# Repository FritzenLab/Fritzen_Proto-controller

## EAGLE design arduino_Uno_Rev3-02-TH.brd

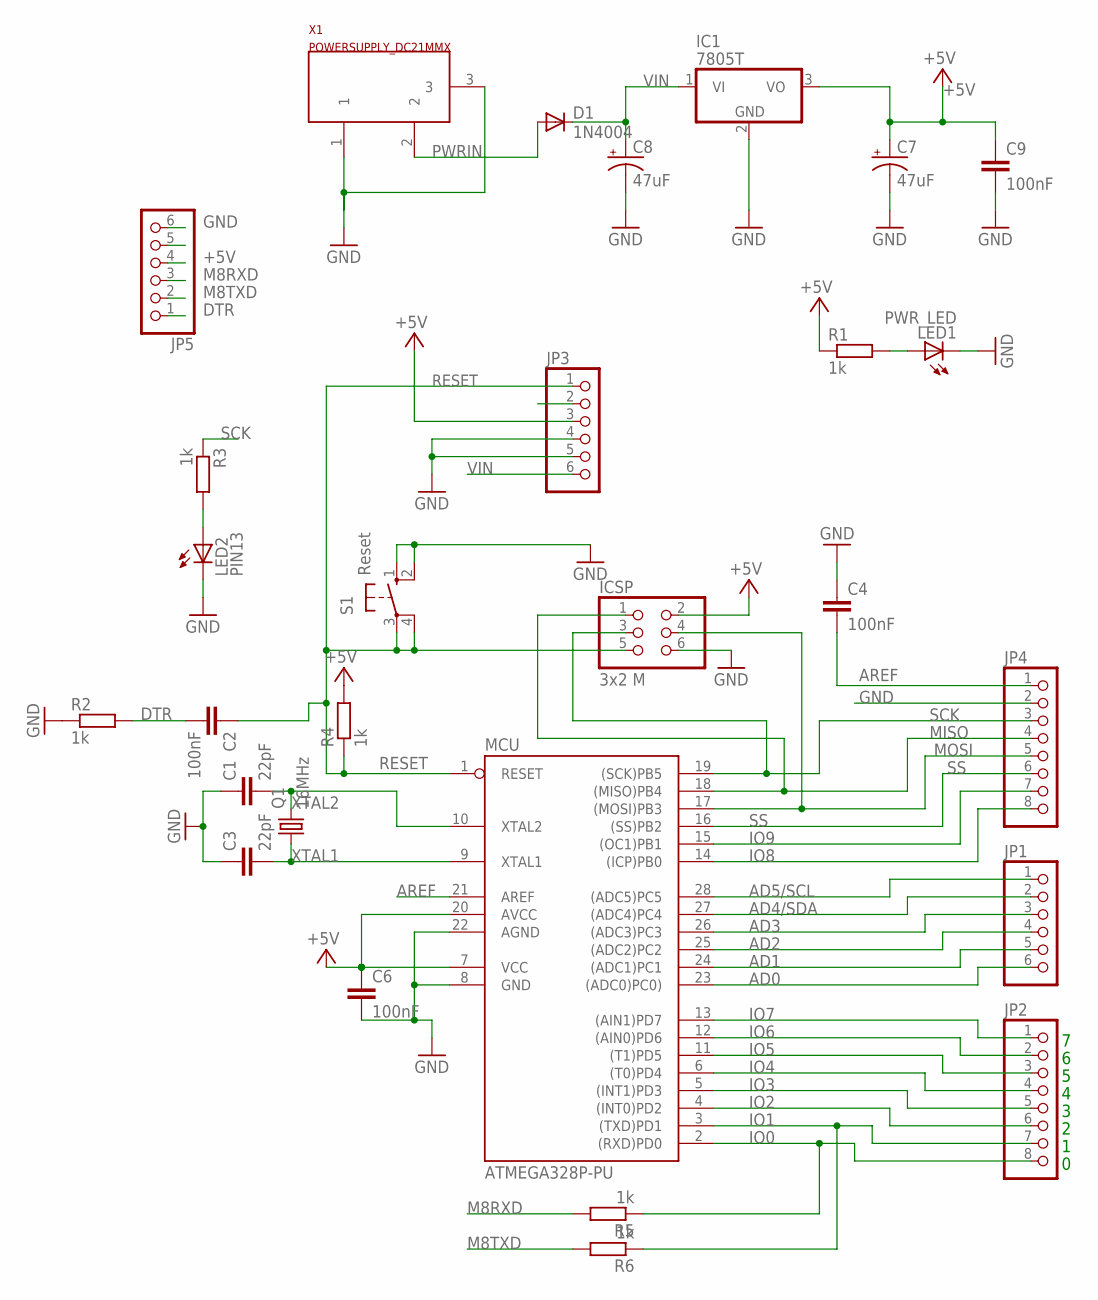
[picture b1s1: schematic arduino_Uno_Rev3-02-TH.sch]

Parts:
C1, C3: 22pF; C2.5-2
C2, C4, C6, C9: 100nF; C2.5-3
C7, C8: 47uF; E3,5-8
D1: 1N4004; DO41-10
IC1: 7805T; TO220H
ICSP: 3x2 M; 2X03
JP1, JP3, JP5: PINHD-1X6; 1X06
JP2, JP4: PINHD-1X8BIG; 1X08-BIG
LED1: PWR_LED; LED3MM
LED2: PIN13; LED5MM
MCU: ATMEGA328P-PU; DIL28-3
Q1: 16MHz; HC49/S
R1, R2, R3, R4, R5, R6: 1k; 0207/10
S1: Reset; B3F-10XX
X1: POWERSUPPLY_DC21MMX; POWERSUPPLY_DC-21MM

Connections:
+5V: C6.1, C7.+, C9.1, IC1.3 (VO), ICSP.2, JP3.3, JP5.4, MCU.7 (VCC), MCU.20 (AVCC), R1.1, R4.2
AD0: JP1.6, MCU.23 ((ADC0)PC0))
AD1: JP1.5, MCU.24 ((ADC1)PC1)
AD2: JP1.4, MCU.25 ((ADC2)PC2)
AD3: JP1.3, MCU.26 ((ADC3)PC3)
AD4/SDA: JP1.2, MCU.27 ((ADC4)PC4)
AD5/SCL: JP1.1, MCU.28 ((ADC5)PC5)
AREF: C4.2, JP4.1, MCU.21 (AREF)
DTR: C2.2, JP5.1, R2.2
GND: C1.1, C3.1, C4.1, C6.2, C7.-, C8.-, C9.2, IC1.2 (GND), ICSP.6, JP3.4, JP3.5, JP4.2, JP5.6, LED1.K (C), LED2.K (C), MCU.8 (GND), MCU.22 (AGND), R2.1, S1.1 (S), S1.2 (S1), X1.1, X1.3
IO0: JP2.8, MCU.2 ((RXD)PD0), R5.1
IO1: JP2.7, MCU.3 ((TXD)PD1), R6.1
IO2: JP2.6, MCU.4 ((INT0)PD2)
IO3: JP2.5, MCU.5 ((INT1)PD3)
IO4: JP2.4, MCU.6 ((T0)PD4)
IO5: JP2.3, MCU.11 ((T1)PD5)
IO6: JP2.2, MCU.12 ((AIN0)PD6)
IO7: JP2.1, MCU.13 ((AIN1)PD7)
IO8: JP4.8, MCU.14 ((ICP)PB0)
IO9: JP4.7, MCU.15 ((OC1)PB1)
M8RXD: JP5.3, R5.2
M8TXD: JP5.2, R6.2
MISO: ICSP.1, JP4.4, MCU.18 ((MISO)PB4)
MOSI: ICSP.4, JP4.5, MCU.17 ((MOSI)PB3)
unnamed: LED2.A, R3.2
unnamed: LED1.A, R1.2
PWRIN: D1.A, X1.2
RESET: C2.1, ICSP.5, JP3.1, MCU.1 (RESET), R4.1, S1.3, S1.4 (P1)
SCK: ICSP.3, JP4.3, MCU.19 ((SCK)PB5), R3.1
SS: JP4.6, MCU.16 ((SS)PB2)
VIN: C8.+, D1.C, IC1.1 (VI), JP3.6
XTAL1: C3.2, MCU.9 (XTAL1), Q1.1
XTAL2: C1.2, MCU.10 (XTAL2), Q1.2

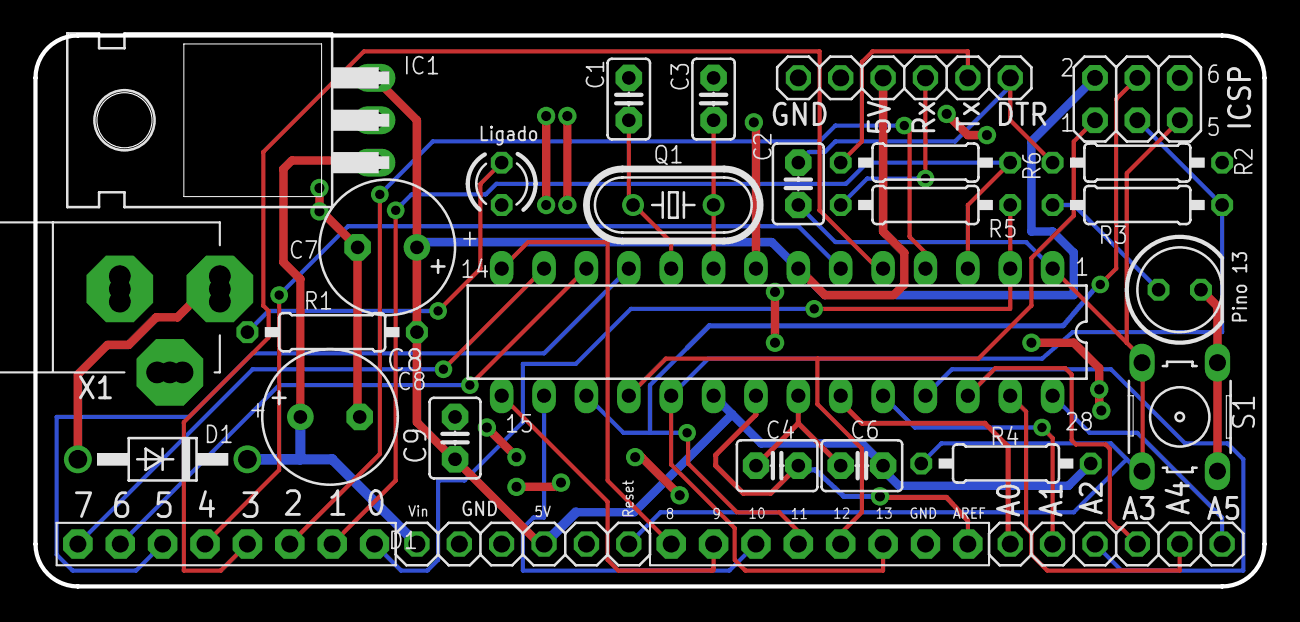
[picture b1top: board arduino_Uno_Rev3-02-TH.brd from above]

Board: 2 copper layers, 73.7 x 33.0 mm, 28 parts (0 on the bottom side), 33 nets.

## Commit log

2016-02-12 Primeira revisão do Arduino para Protoboard
    Um compatível com Arduino para ser montado na vertical em protoboard
    (Fritzen Proto)
2016-02-23 Second revision of the breadboard-mountable Arduino
    Second revision of the breadboard-mountable Arduino, making use of
    better parts (using Adafruit and Sparkfun libraries) and positioning
    silkscreen smartly.
2016-03-23 Third revision and Fabrication Files
    I have ordered 30 pieces of this PCB at MakerStudio.CC on 03/23/2016
